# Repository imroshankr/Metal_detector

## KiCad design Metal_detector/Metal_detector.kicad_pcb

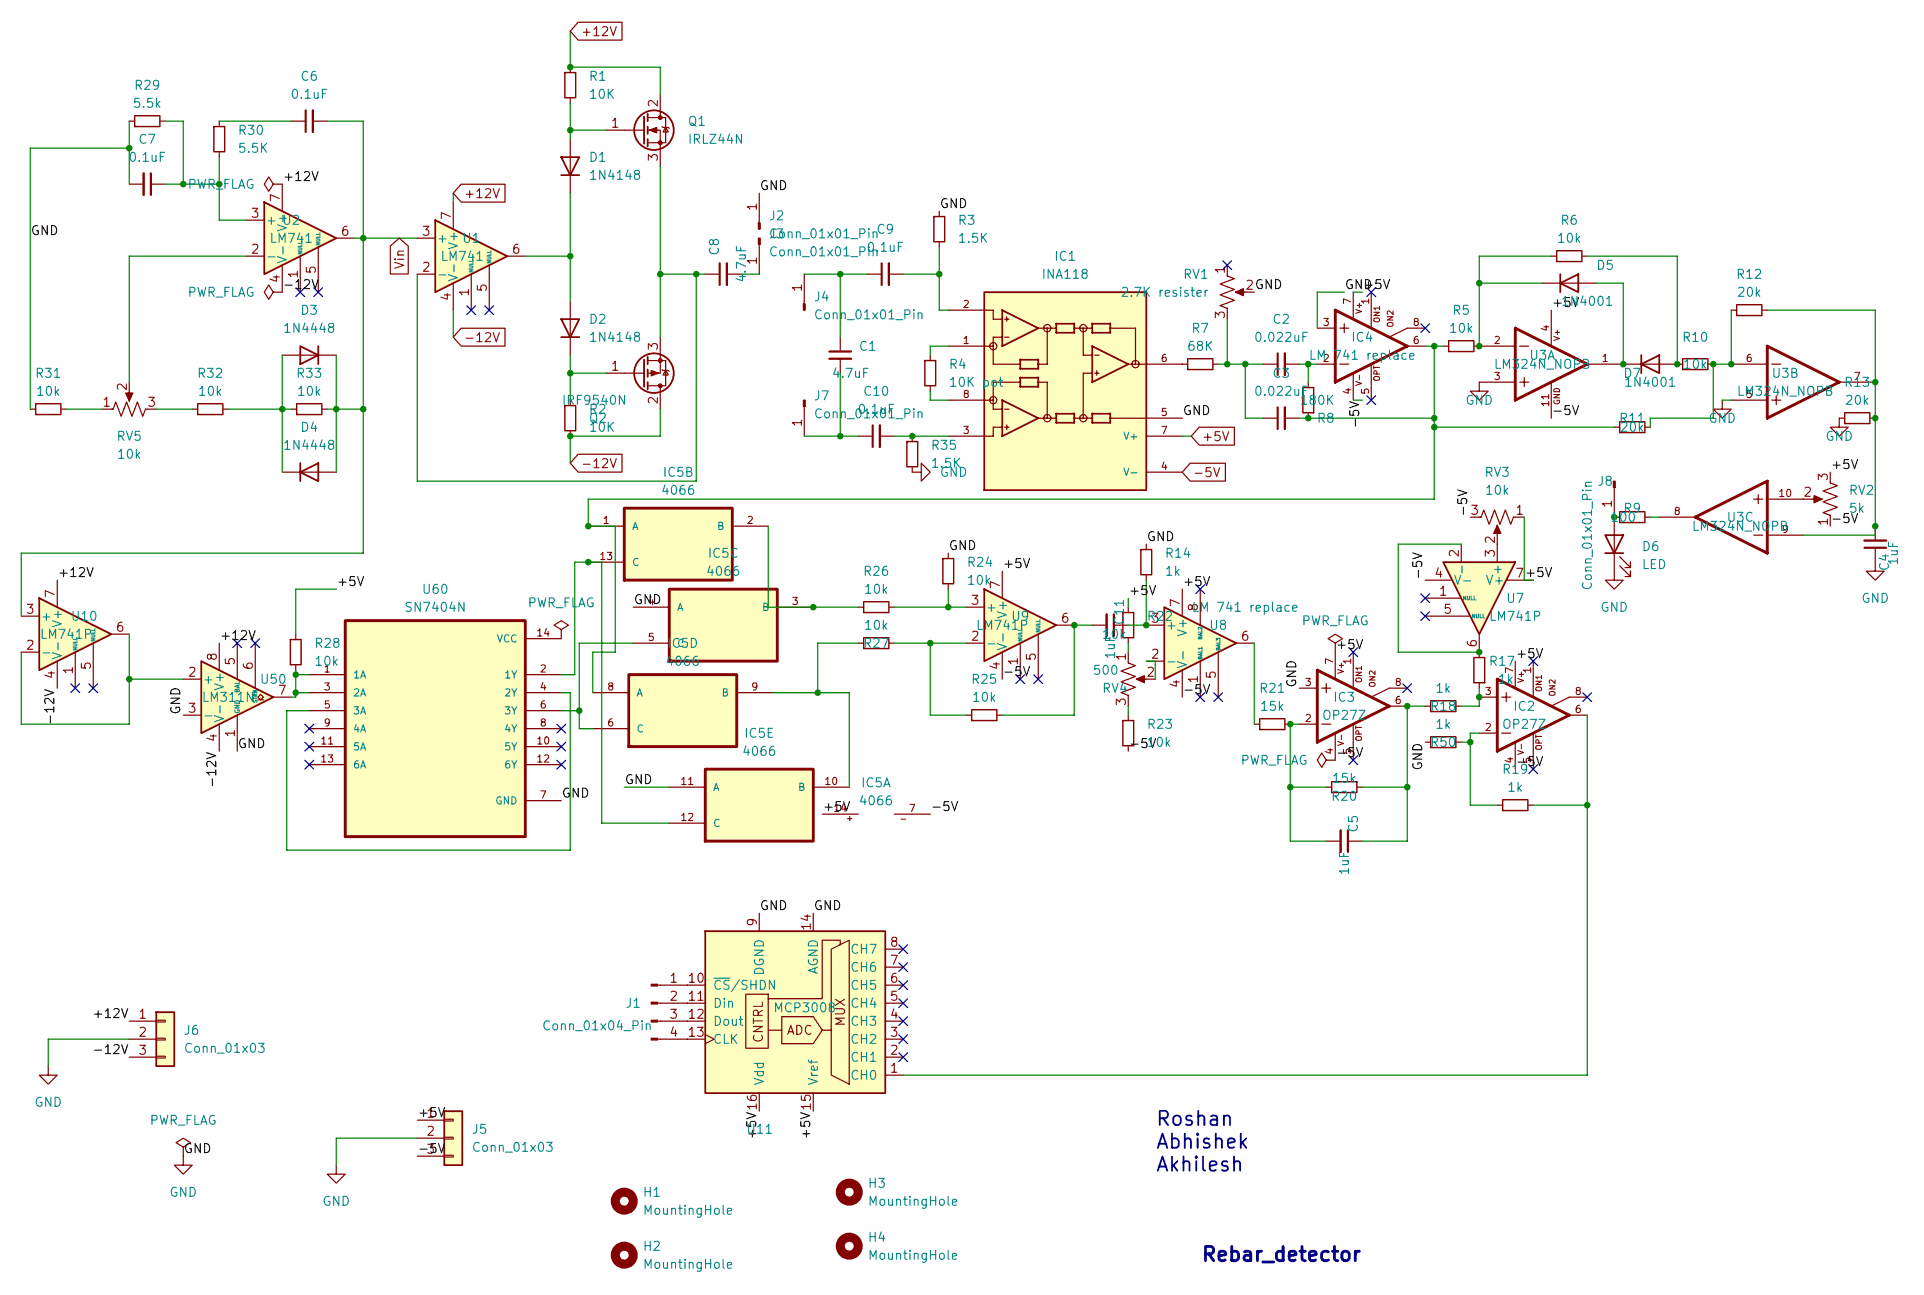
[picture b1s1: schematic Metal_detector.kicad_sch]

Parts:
C1, C8: 4.7uF; C_Radial_D6.3mm_H5.0mm_P2.50mm
C2, C3: 0.022uF; C_Disc_D5.0mm_W2.5mm_P2.50mm
C4: 1uF; C_Disc_D5.0mm_W2.5mm_P2.50mm
C5, C11: 1uF; C_Radial_D6.3mm_H5.0mm_P2.50mm
C6, C7: 0.1uF; C_Disc_D3.8mm_W2.6mm_P2.50mm
C9, C10: 0.1uF; C_Disc_D5.0mm_W2.5mm_P2.50mm
D1, D2: 1N4148; D_DO-35_SOD27_P7.62mm_Horizontal
D3, D4: 1N4448; D_DO-35_SOD27_P7.62mm_Horizontal
D5, D7: 1N4001; D_DO-41_SOD81_P10.16mm_Horizontal
D6: LED; LED_D3.0mm
H1, H2, H3, H4: MountingHole; MountingHole_3mm
IC1: INA118; DIP-8_W7.62mm_LongPads; MPN INA118U
IC2, IC3: OP27Z; DIP-8_W7.62mm_LongPads
IC4: LM 741 replace; DIP-8_W7.62mm_LongPads
IC5: 4066; DIP-14_W7.62mm_Socket_LongPads
J1: Conn_01x04_Pin; PinHeader_1x04_P2.54mm_Vertical
J2, J3, J4, J7, J8: Conn_01x01_Pin; Pin_D1.1mm_L10.2mm_W3.5mm_Flat
J5, J6: Conn_01x03; PinHeader_1x03_P2.54mm_Vertical
Q1: IRLZ44N; TO-220-3_Vertical
Q2: IRF9540N; TO-220-3_Vertical
R1, R2: 10K; R_Axial_DIN0204_L3.6mm_D1.6mm_P7.62mm_Horizontal
R3, R35: 1.5K; R_Axial_DIN0204_L3.6mm_D1.6mm_P7.62mm_Horizontal
R4: 10K pot; R_Axial_DIN0204_L3.6mm_D1.6mm_P7.62mm_Horizontal
R5, R6, R10, R22, R23, R24, R25, R26, R27, R28, R31, R32, R33: 10k; R_Axial_DIN0204_L3.6mm_D1.6mm_P7.62mm_Horizontal
R7: 68K; R_Axial_DIN0204_L3.6mm_D1.6mm_P7.62mm_Horizontal
R8: 180K; R_Axial_DIN0204_L3.6mm_D1.6mm_P7.62mm_Horizontal
R9: 100; R_Axial_DIN0204_L3.6mm_D1.6mm_P7.62mm_Horizontal
R11, R12, R13: 20k; R_Axial_DIN0204_L3.6mm_D1.6mm_P7.62mm_Horizontal
R14, R17, R18, R19, R50: 1k; R_Axial_DIN0204_L3.6mm_D1.6mm_P7.62mm_Horizontal
R20, R21: 15k; R_Axial_DIN0204_L3.6mm_D1.6mm_P7.62mm_Horizontal
R29: 5.5k; R_Axial_DIN0204_L3.6mm_D1.6mm_P7.62mm_Horizontal
R30: 5.5K; R_Axial_DIN0204_L3.6mm_D1.6mm_P7.62mm_Horizontal
RV1: 2.7K resister; Potentiometer_ACP_CA14-H5_Horizontal
RV2: 5k; Potentiometer_Bourns_3386F_Vertical
RV3, RV5: 10k; Potentiometer_ACP_CA14-H5_Horizontal
RV4: 500; Potentiometer_ACP_CA14-H5_Horizontal
U1, U2: LM741; DIP-8_W7.62mm
U3: LM324N_NOPB; DIP825W47P254L1917H533Q14; PARTREV D
U7, U9, U10: LM741P; DIP-8_W7.62mm
U8: LM 741 replace; DIP-8_W7.62mm
U11: MCP3008; DIP-16_W7.62mm
U50: LM311N; DIP-8_W7.62mm
U60: SN7404N; DIP794W45P254L1969H508Q14

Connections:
+5V: IC1.7 (V+), IC2.7, IC3.7, IC4.7, IC5.14, J5.1, R22.1, R28.1, RV2.3, RV3.1, U3.4, U7.7 (V+), U8.7 (V+), U9.7 (V+), U11.15 (Vref), U11.16 (Vdd)
+12V: J6.1, Q1.2 (D), R1.1, U1.7 (V+), U2.7 (V+), U10.7 (V+), U50.8 (V+)
-5V: IC1.4 (V-), IC2.4, IC3.4, IC4.4, IC5.7, J5.3, R23.2, RV2.1, RV3.3, U3.11, U7.4 (V-), U8.4 (V-), U9.4 (V-)
-12V: J6.3, Q2.2 (D), R2.2, U1.4 (V-), U2.4 (V-), U10.4 (V-), U50.4 (V-)
GND: C4.1, C7.2, D6.1 (K), IC1.5, IC3.3, IC4.3, IC5.4 (A), IC5.11 (A), J2.1, J5.2, J6.2, R3.1, R13.1, R14.1, R24.1, R29.1, R31.1, R35.2, R50.1, RV1.2, U3.3, U3.5, U11.9 (DGND), U11.14 (AGND), U50.1 (GND), U50.3 (-), U60.7 (GND)
unnamed: C2.1, C3.1, R7.2, RV1.3
unnamed: C2.2, IC4.2, R8.2
unnamed: C4.2, R12.2, R13.2, U3.7, U3.9
unnamed: C5.1, IC3.6, R18.1, R20.1
unnamed: C5.2, IC3.2, R20.2, R21.2
unnamed: C6.1, R30.1
unnamed: C9.2, IC1.2, R3.2
unnamed: C10.2, IC1.3, R35.1
unnamed: C11.2, R25.2, U9.6
unnamed: D1.2 (A), Q1.1 (G), R1.2
unnamed: D1.1 (K), D2.2 (A), U1.6
unnamed: D2.1 (K), Q2.1 (G), R2.1
unnamed: D3.2 (A), D4.1 (K), R32.2, R33.1
unnamed: D5.2 (A), D7.1 (K), U3.1
unnamed: D5.1 (K), R5.2, R6.1, U3.2
unnamed: D6.2 (A), J8.1, R9.1
unnamed: D7.2 (A), R6.2, R10.1
unnamed: IC1.1, R4.1
unnamed: IC1.6, R7.1
unnamed: IC1.8, R4.2
unnamed: IC2.2, R19.1, R50.2
unnamed: IC2.3, R17.1, R18.2
unnamed: C3.2, IC4.6, IC5.1 (A), IC5.8 (A), R5.1, R8.1, R11.1
unnamed: IC5.2 (B), IC5.3 (B), R26.1
unnamed: IC5.12 (C), IC5.13 (C), U60.2 (1Y)
unnamed: IC5.5 (C), IC5.6 (C), U60.6 (3Y)
unnamed: IC5.9 (B), IC5.10 (B), R27.1
unnamed: J1.1, U11.10 (~CS/SHDN)
unnamed: J1.2, U11.11 (Din)
unnamed: J1.3, U11.12 (Dout)
unnamed: J1.4, U11.13 (CLK)
unnamed: C8.2, J3.1
unnamed: C1.1, C9.1, J4.1
unnamed: C1.2, C10.1, J7.1
unnamed: C8.1, Q1.3 (S), Q2.3 (S), U1.2 (-)
unnamed: R9.2, U3.8
unnamed: R10.2, R11.2, R12.1, U3.6
unnamed: R21.1, U8.6
unnamed: R22.2, RV4.1
unnamed: R23.1, RV4.3
unnamed: R31.2, RV5.1
unnamed: R32.1, RV5.3
unnamed: RV2.2, U3.10
unnamed: C7.1, R29.2, R30.2, U2.3 (+)
unnamed: RV5.2, U2.2 (-)
unnamed: RV3.2, U7.3 (+)
unnamed: R17.2, U7.2 (-), U7.6
unnamed: C11.1, R14.2, U8.3 (+)
unnamed: RV4.2, U8.2 (-)
unnamed: R24.2, R26.2, U9.3 (+)
unnamed: R25.1, R27.2, U9.2 (-)
unnamed: U10.2 (-), U10.6, U50.2 (+)
unnamed: IC2.6, R19.2, U11.1 (CH0)
unnamed: R28.2, U50.7, U60.1 (1A), U60.3 (2A)
unnamed: U60.4 (2Y), U60.5 (3A)
Vin: C6.2, D3.1 (K), D4.2 (A), R33.2, U1.3 (+), U2.6, U10.3 (+)

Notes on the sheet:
Rebar_detector
Roshan Abhishek Akhilesh

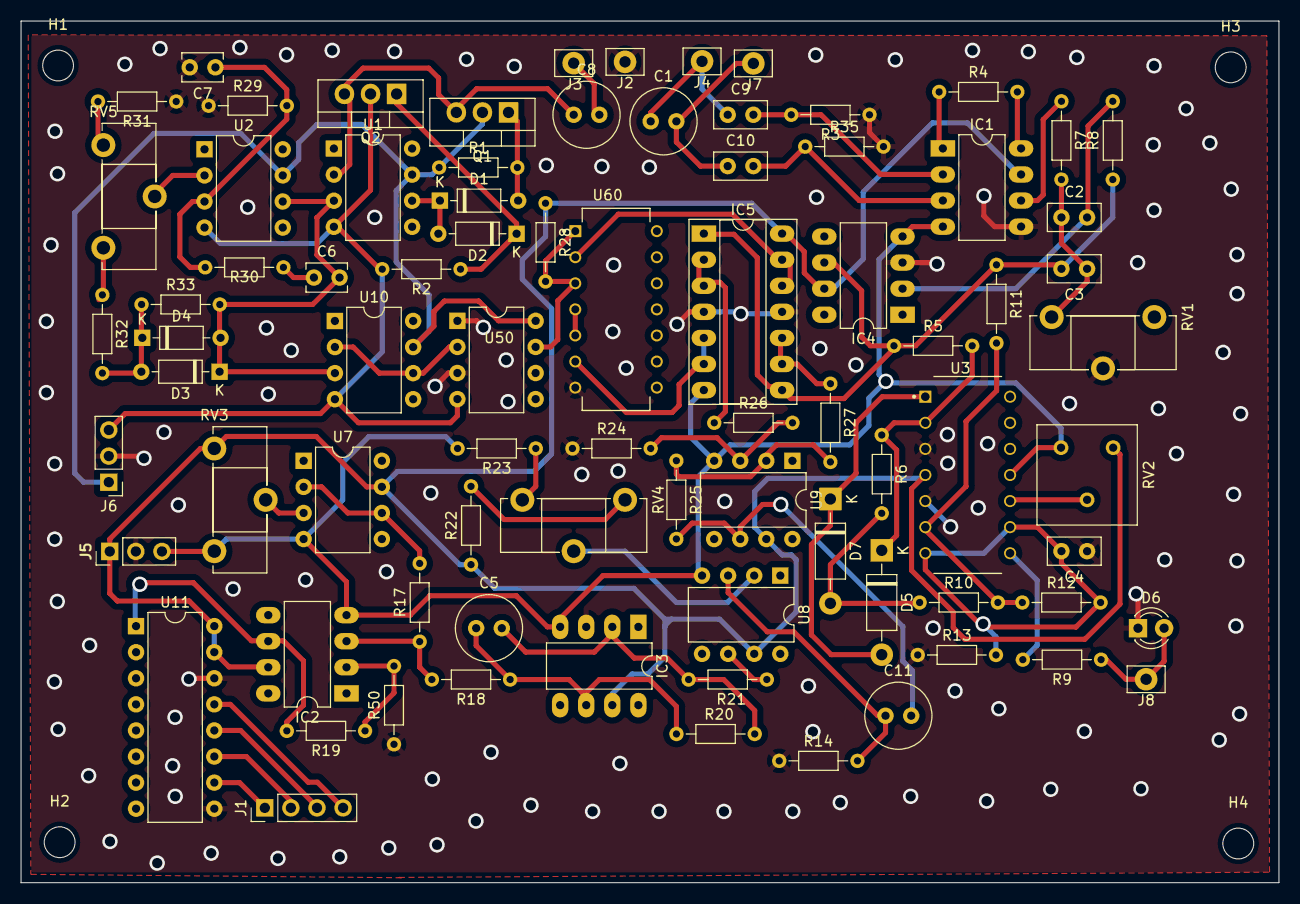
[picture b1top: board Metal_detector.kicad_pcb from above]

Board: 2 copper layers, 122.5 x 83.9 mm, 85 parts (0 on the bottom side), 61 nets.

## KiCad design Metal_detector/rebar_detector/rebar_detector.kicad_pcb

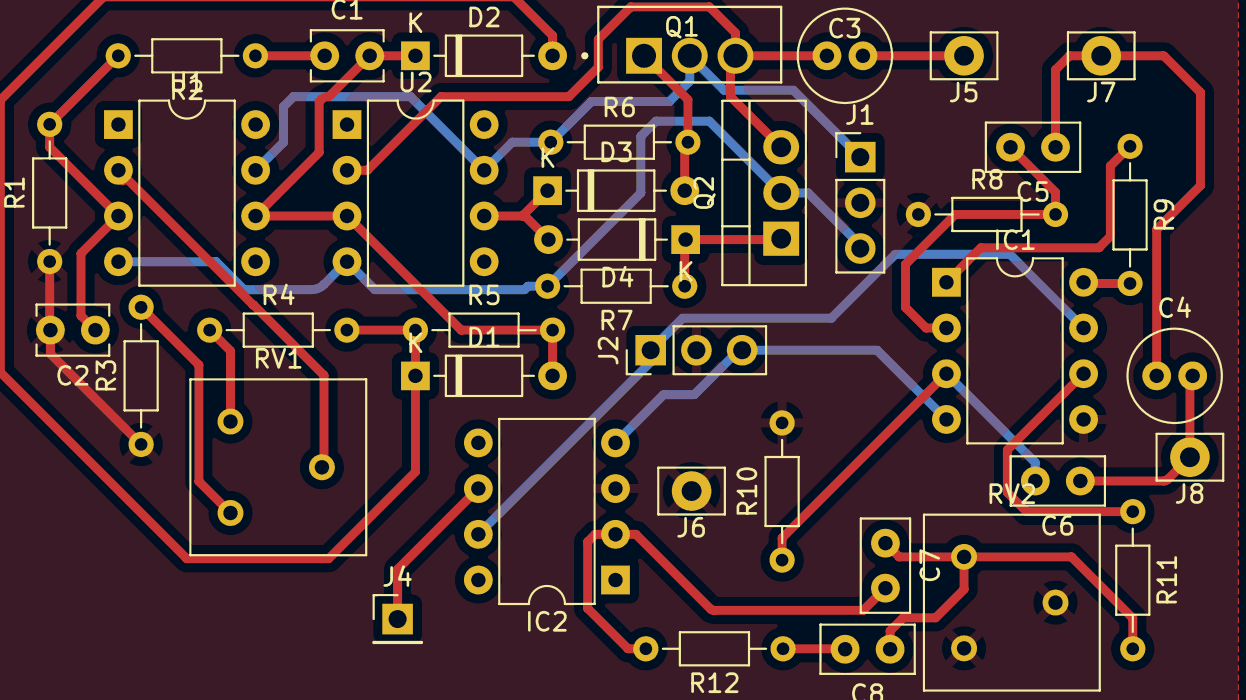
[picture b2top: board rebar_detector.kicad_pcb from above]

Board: 2 copper layers, 39 parts (0 on the bottom side), 28 nets.

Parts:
C1, C2: 22pF; C_Disc_D3.8mm_W2.6mm_P2.50mm
C3, C4: 4.7uF; C_Radial_D5.0mm_H11.0mm_P2.00mm
C5, C6, C7, C8: 0.1uF; C_Disc_D5.0mm_W2.5mm_P2.50mm
D1, D2: 1N4448; D_DO-35_SOD27_P7.62mm_Horizontal
D3, D4: 1N4148; D_DO-35_SOD27_P7.62mm_Horizontal
IC1: INA118; DIP-8_W7.62mm
IC2: OP27Z; DIP-8_W7.62mm
J1, J2: Conn_01x03; PinHeader_1x03_P2.54mm_Vertical
J4: Conn_01x01; PinHeader_1x01_P2.54mm_Vertical
J5, J6, J7, J8: Conn_01x01_Pin; Pin_D1.1mm_L10.2mm_W3.5mm_Flat
Q1: IRFZ44N; TO254P1016X419X2286-3
Q2: IRF9540N; TO-220-3_Vertical
R1: 1.3k; R_Axial_DIN0204_L3.6mm_D1.6mm_P7.62mm_Horizontal
R2: 1.3K; R_Axial_DIN0204_L3.6mm_D1.6mm_P7.62mm_Horizontal
R3, R4, R5: 10k; R_Axial_DIN0204_L3.6mm_D1.6mm_P7.62mm_Horizontal
R6, R7: 10K; R_Axial_DIN0204_L3.6mm_D1.6mm_P7.62mm_Horizontal
R8, R10: 1.7K; R_Axial_DIN0204_L3.6mm_D1.6mm_P7.62mm_Horizontal
R9: 470; R_Axial_DIN0204_L3.6mm_D1.6mm_P7.62mm_Horizontal
R11: 7.6k; R_Axial_DIN0204_L3.6mm_D1.6mm_P7.62mm_Horizontal
R12: 30.47k; R_Axial_DIN0204_L3.6mm_D1.6mm_P7.62mm_Horizontal
RV1: 10k; Potentiometer_Bourns_3386F_Vertical
RV2: 100; Potentiometer_Bourns_3386F_Vertical
U1, U2: LM741; DIP-8_W7.62mm

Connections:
+12V: J1.1, Q1.2, R6.1, U1.7 (V+), U2.7 (V+)
-12V: J1.3, Q2.2 (D), R7.2, U1.4 (V-), U2.4 (V-)
/+5V: IC1.7 (V+), IC2.7, J2.1
/-5V: IC1.4 (V-), IC2.4, J2.3
GND: C2.2, IC1.5, IC2.3, J1.2, J2.2, J6.1, R1.1, R3.1, R8.1, R10.2, RV2.1, RV2.2
unnamed: C1.1, R2.1
unnamed: C5.2, IC1.2, R8.2
unnamed: C6.2, IC1.3, R10.1
unnamed: C7.1, C8.1, R11.2, RV2.3
unnamed: C7.2, IC2.2, R12.2
unnamed: C8.2, R12.1
unnamed: C1.2, D1.2 (A), D2.1 (K), R5.2, U1.6, U2.3 (+)
unnamed: D1.1 (K), D2.2 (A), R4.2, R5.1
unnamed: D3.2 (A), Q1.1, R6.2
unnamed: D3.1 (K), D4.2 (A), U2.6
unnamed: D4.1 (K), Q2.1 (G), R7.1
unnamed: IC1.1, R9.1
unnamed: IC1.6, R11.1
unnamed: IC1.8, R9.2
unnamed: IC2.6, J4.1
unnamed: C3.2, J5.1
unnamed: C4.1, C5.1, J7.1
unnamed: C4.2, C6.1, J8.1
unnamed: C3.1, Q1.3, Q2.3 (S), U2.2 (-)
unnamed: R3.2, RV1.1
unnamed: R4.1, RV1.3
unnamed: C2.1, R1.2, R2.2, U1.3 (+)
unnamed: RV1.2, U1.2 (-)
